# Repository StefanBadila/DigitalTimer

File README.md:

# DigitalTimer

The project is a digital timer that counts up to 60 seconds, displaying numbers on 7-segment displays. Each 4-bit output from the counters is converted via a binary-to-7-segment decoder. The circuit includes start/stop and reset switches for controlling the timer's operation.

# Description
My Digital Timer project involves creating a PCB circuit for a timer counting up to 60 seconds. It uses a 1 Hz clock signal generated by an NE555 oscillator, connected to counters for seconds and tens of seconds. The 4-bit output is decoded to drive 7-segment displays. Components include 7-segment displays, 4-bit counters, decoders, logic gates, and a JK flip-flop. The circuit has switches for start/stop and reset. Design was completed in KiCad with a 2-layer, 9 cm x 7 cm PCB layout.

# Steps 

Step 1: Creating the schematic for this circuit using KiCad

Step 2: Creating the PCB, placing parts on PCB, drawing traces beetween parts and final touches for the PCB

Step 3: Order all the parts, the PCB and put it all toghether

# Contents

| File/folder | Description |
|-------------|-------------|
| `digitaltimer.kicad_sch`       | Schematic |
| `digitaltimer.kicad_pcb`       | PCB editor |
| `digitaltimer.kicad_pro`       | KiCad project file |
| `digitaltimer.kicad_prl`       | KiCad project rules |
| `README.md` | This README file. |

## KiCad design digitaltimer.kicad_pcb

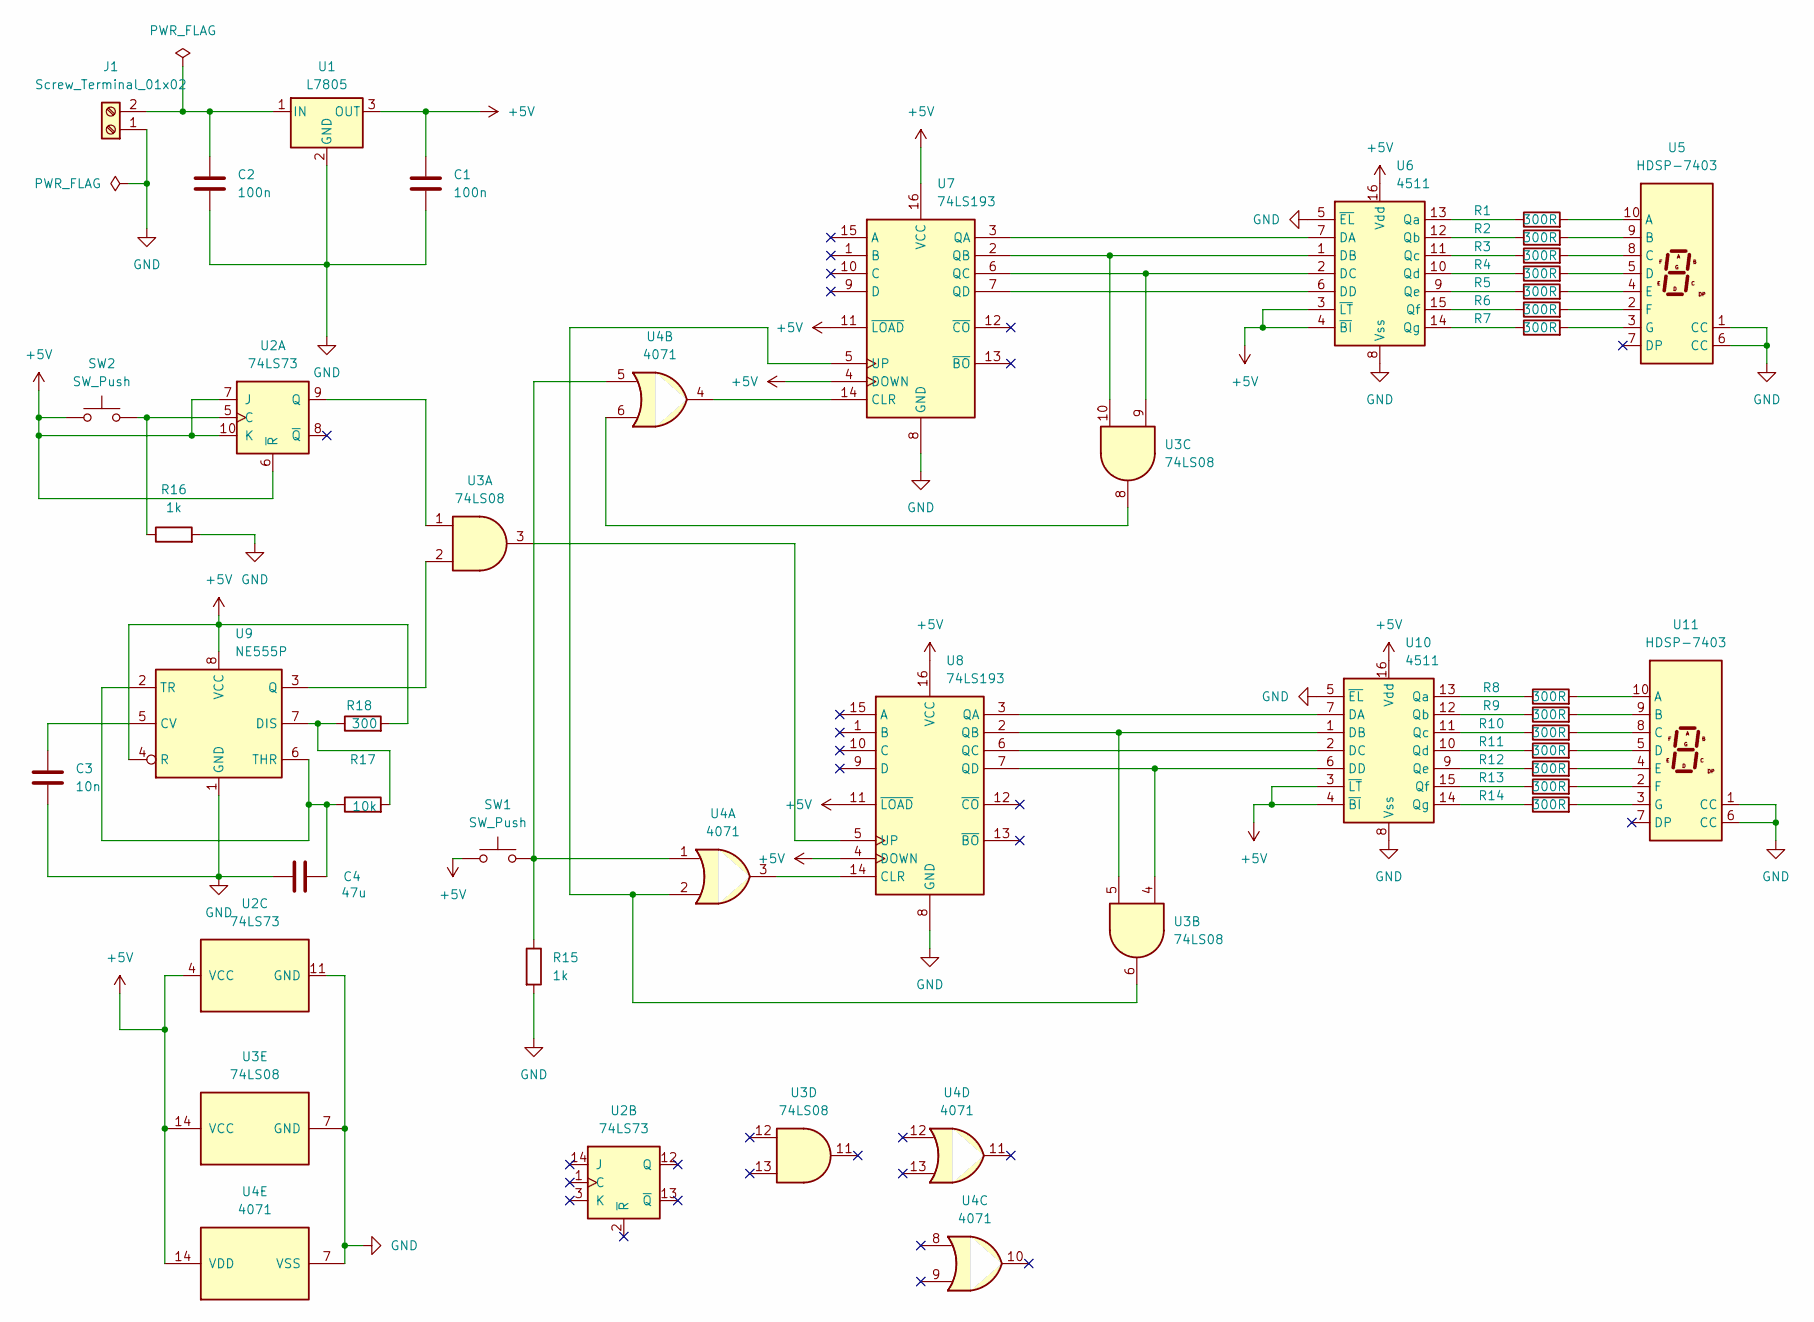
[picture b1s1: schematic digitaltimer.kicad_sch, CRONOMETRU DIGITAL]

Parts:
C1, C2: 100n; C_Disc_D3.0mm_W2.0mm_P2.50mm
C3: 10n; C_Rect_L7.0mm_W2.5mm_P5.00mm
C4: 47u; C_Radial_D5.0mm_H11.0mm_P2.00mm
J1: Screw_Terminal_01x02; TerminalBlock_Altech_AK300-2_P5.00mm
R1, R2, R3, R4, R5, R6, R7, R8, R9, R10, R11, R12, R13, R14: 300R; R_Axial_DIN0204_L3.6mm_D1.6mm_P5.08mm_Horizontal
R15, R16: 1k; R_Axial_DIN0204_L3.6mm_D1.6mm_P5.08mm_Horizontal
R17: 10k; R_Axial_DIN0204_L3.6mm_D1.6mm_P5.08mm_Horizontal
R18: 300; R_Axial_DIN0204_L3.6mm_D1.6mm_P5.08mm_Horizontal
SW1, SW2: SW_Push; SW_PUSH_6mm
U1: L7805; TO-220-3_Vertical
U2: 74LS73; DIP-14_W7.62mm
U3: 74LS08; DIP-14_W7.62mm
U4: 4071; DIP-14_W7.62mm
U5, U11: HDSP-7403; HDSP-7401
U6, U10: 4511; DIP-16_W7.62mm
U7, U8: 74LS193; DIP-16_W7.62mm
U9: NE555P; DIP-8_W7.62mm

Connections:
GND: C1.2, C2.2, C3.1, C4.1, J1.1, R15.2, R16.2, U1.2 (GND), U2.11 (GND), U3.7 (GND), U4.7 (VSS), U5.1 (CC), U5.6 (CC), U6.5 (~EL), U6.8 (Vss), U7.8 (GND), U8.8 (GND), U9.1 (GND), U10.5 (~EL), U10.8 (Vss), U11.1 (CC), U11.6 (CC)
unnamed: C2.1, J1.2, U1.1 (IN)
unnamed: R15.1, SW1.2, U4.1, U4.5
unnamed: R16.1, SW2.2, U2.5 (C)
unnamed: U2.9 (Q), U3.1
unnamed: U3.8, U4.6
unnamed: R1.2, U5.10 (A)
unnamed: R2.2, U5.9 (B)
unnamed: R3.2, U5.8 (C)
unnamed: R4.2, U5.5 (D)
unnamed: R5.2, U5.4 (E)
unnamed: R6.2, U5.2 (F)
unnamed: R7.2, U5.3 (G)
unnamed: U6.7 (DA), U7.3 (QA)
unnamed: U3.10, U6.1 (DB), U7.2 (QB)
unnamed: U3.9, U6.2 (DC), U7.6 (QC)
unnamed: U6.6 (DD), U7.7 (QD)
unnamed: R1.1, U6.13 (Qa)
unnamed: R2.1, U6.12 (Qb)
unnamed: R3.1, U6.11 (Qc)
unnamed: R4.1, U6.10 (Qd)
unnamed: R5.1, U6.9 (Qe)
unnamed: R6.1, U6.15 (Qf)
unnamed: R7.1, U6.14 (Qg)
unnamed: U4.4, U7.14 (CLR)
unnamed: U3.6, U4.2, U7.5 (UP)
unnamed: U4.3, U8.14 (CLR)
unnamed: U3.3, U8.5 (UP)
unnamed: C3.2, U9.5 (CV)
unnamed: R17.2, R18.1, U9.7 (DIS)
unnamed: U3.2, U9.3 (Q)
unnamed: U8.3 (QA), U10.7 (DA)
unnamed: U3.5, U8.2 (QB), U10.1 (DB)
unnamed: U8.6 (QC), U10.2 (DC)
unnamed: U3.4, U8.7 (QD), U10.6 (DD)
unnamed: R8.1, U10.13 (Qa)
unnamed: R9.1, U10.12 (Qb)
unnamed: R10.1, U10.11 (Qc)
unnamed: R11.1, U10.10 (Qd)
unnamed: R12.1, U10.9 (Qe)
unnamed: R13.1, U10.15 (Qf)
unnamed: R14.1, U10.14 (Qg)
unnamed: R8.2, U11.10 (A)
unnamed: R9.2, U11.9 (B)
unnamed: R10.2, U11.8 (C)
unnamed: R11.2, U11.5 (D)
unnamed: R12.2, U11.4 (E)
unnamed: R13.2, U11.2 (F)
unnamed: R14.2, U11.3 (G)

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
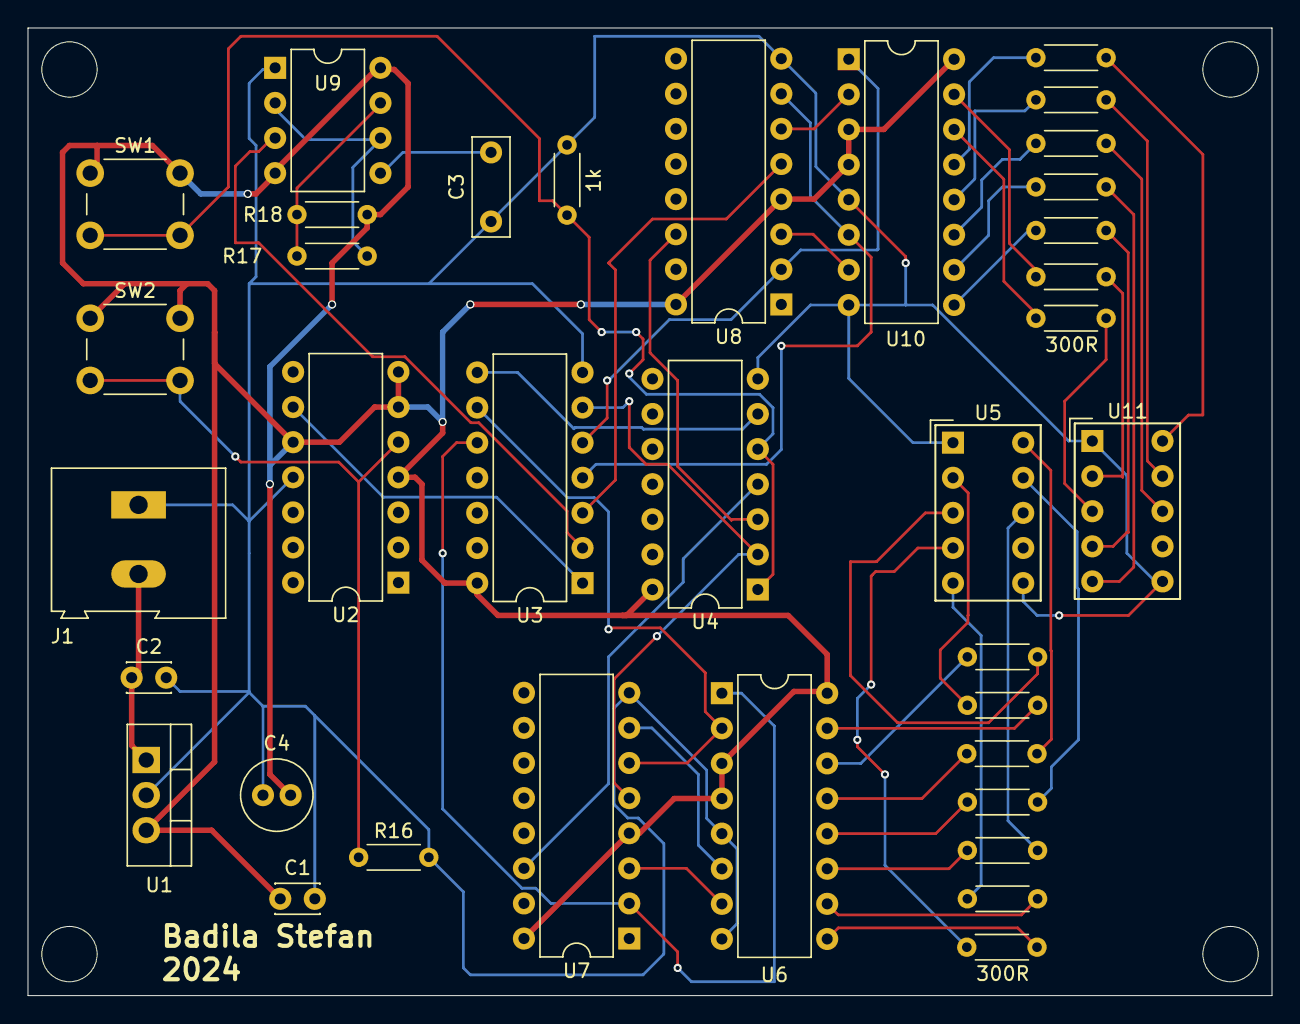
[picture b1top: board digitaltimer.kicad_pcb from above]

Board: 2 copper layers, 90.0 x 70.0 mm, 36 parts (0 on the bottom side), 51 nets.
